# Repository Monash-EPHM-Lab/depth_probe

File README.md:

# depth probe
Repository for Monash BoSL depth probe

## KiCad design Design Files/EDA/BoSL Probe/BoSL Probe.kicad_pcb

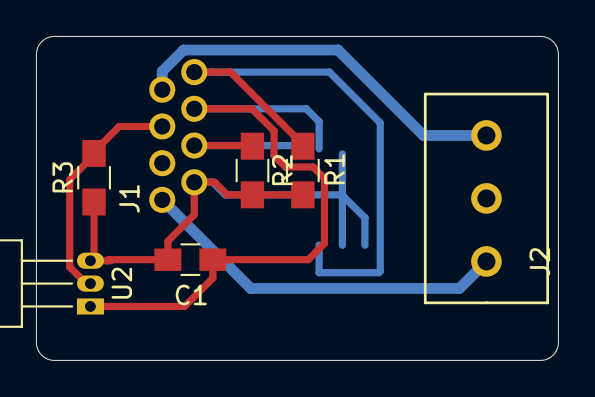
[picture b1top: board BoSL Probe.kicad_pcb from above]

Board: 2 copper layers, 29.0 x 18.0 mm, 8 parts (1 on the bottom side), 7 nets.

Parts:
C1: 100nF; C_0805_HandSoldering
J1: 8P8C_Shielded; RJ_45
J2: Screw_Terminal_01x03; Screw_Terminals_1x3_3.5mm
R1, R2: 10 kΩ; R_0805_HandSoldering
R3: 4.7 kΩ; R_0805_HandSoldering
U1: MS5803-01BA; MS5803
U2: DS18B20; TO-92_Horizontal2_Inline_Narrow_Oval

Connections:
A0: J1.1, J2.1
A3: J1.7, J2.3
Blue: J1.4, R2.1, U1.1
BlueHalf: J1.5, R3.2, U2.2
Brown: J1.8, R1.2, U1.7
Green: C1.2, J1.6, U1.2, U2.1
Orange: C1.1, J1.2, R1.1, R2.2, R3.1, U1.3, U1.5, U1.6, U2.3

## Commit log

2020-08-16 init
2020-08-16 init files
2020-08-16 added datasheet
2020-08-16 added sleep current
2020-08-18 added diagrams to datasheet
2020-08-19 added first revision of datasheet
2020-08-20 added diagrams and fixed some comments
2020-08-28 added test code
2020-09-06 added rendeders of how to build sensor
2020-10-04 added 3d models of files
